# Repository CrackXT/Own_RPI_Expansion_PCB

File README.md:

# Own_RPI_Expansion_PCB

PCB files for RPI Expansion Board

# Description

This is the expansion board for the mainboard.

- Part 2

A small info display is activated via an MCU and the temperature is read from the mainboard. There is also a mic, light sensor and the rotary switch for switching the streamer on and off (and restarting it), as well as status LEDs. 

The RGB is controlled via the MCU. In addition, the MCU can be reset or booted via separate buttons

The board can be produced here (AISLER) with the files (.brd and .sch) or by any other PCB manufacturer. -> https://aisler.net/

# Serie

- .pro

# Layout

Top<br>

Bottom<br>

Routing/Dimensions(mm)<br>

Schematic<br>
Schematic as .pdf at the top of the page.

# License

Open hardware, use it, mod it, whatever you want, feel free...

# Thanks!

Own design and layout.

# Version - Build

v1.0 - 06.11.2023

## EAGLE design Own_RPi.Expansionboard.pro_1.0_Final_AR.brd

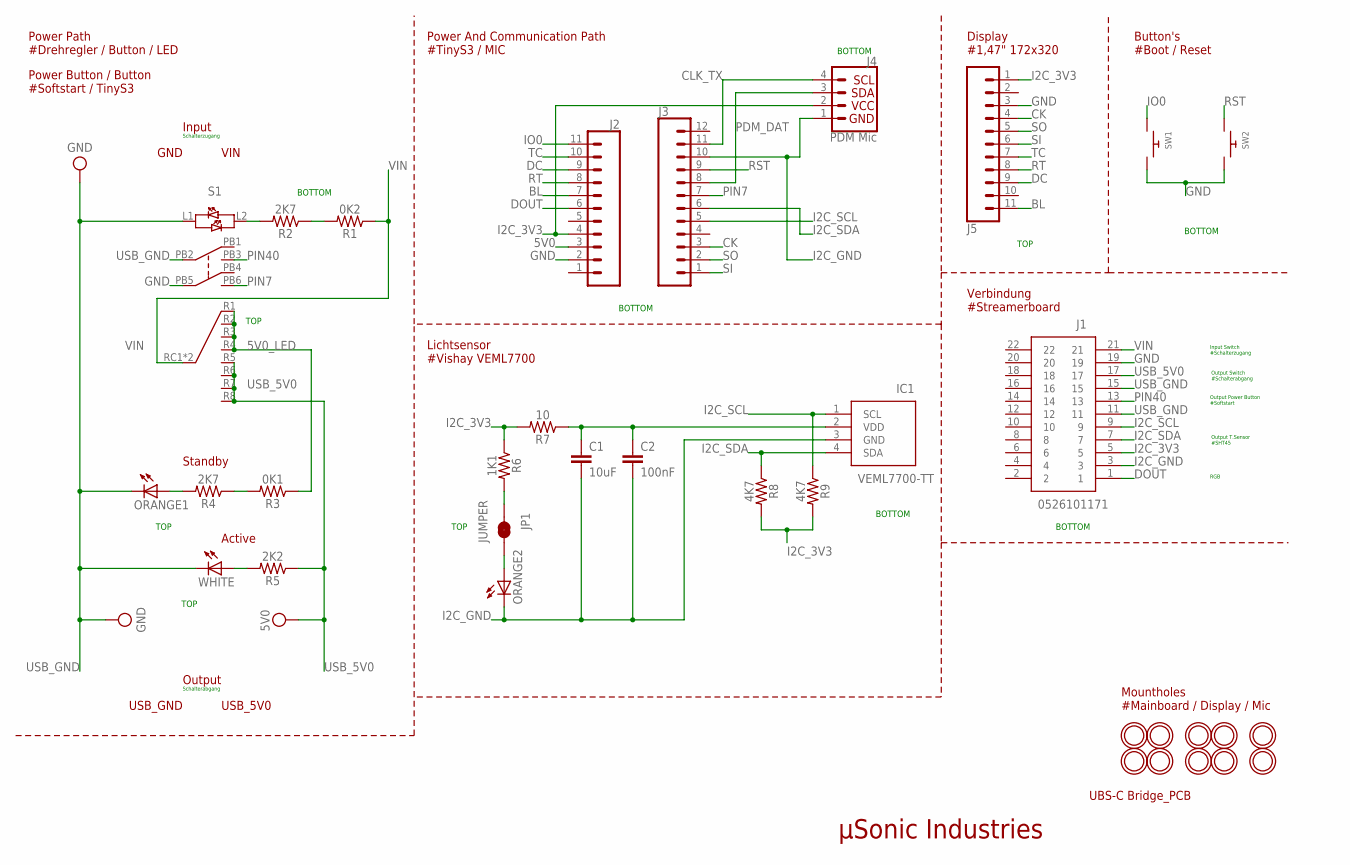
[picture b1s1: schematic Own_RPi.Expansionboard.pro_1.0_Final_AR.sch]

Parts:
C1: 10uF; 0805
C2: 100nF; 0805
IC1: VEML7700-TT; VEML7700
J1: 0526101171
J2, J5: CONN_111X11_NO_SILK; 1X11_NO_SILK
J3: CONN_12NO_SILK; 1X12_NO_SILK
J4: PDM Mic; JST04_1MM_VERT
JP1: JUMPER; SMT-JUMPER_2_NC_TRACE_SILK
ORANGE1, ORANGE2: LEDCHIPLED_0805; CHIPLED_0805
R1: 0K2; 0805
R2, R4: 2K7; 0805
R3: 0K1; 0805
R5: 2K2; 0805
R6: 1K1; 0805
R7: 10; 0805
R8, R9: 4K7; 0805
S1: 481RV12172100
SW1, SW2: SWITCH_PUSHBUTTONSF_OWN; OWN_TACT_PANA-EVQ
U$1, U$2, U$3, U$5, U$8, U$9, U$13, U$14, U$15, U$16: MOUNTINGHOLE2.5; MOUNTINGHOLE_2.5_PLATED
WHITE: LEDCHIPLED_0805; CHIPLED_0805

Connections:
5V0: J2.3
5V0_LED: R3.1, S1.R1, S1.R2, S1.R3, S1.R4
BL: J2.7, J5.11
CK: J3.3, J5.4
CLK_TX: J3.11, J4.4
DC: J2.9, J5.9
DOUT: J1.1, J2.6
GND: J1.19, J2.2, J5.3, S1.PB5, SW1.P$2, SW2.P$2
I2C_3V3: J1.5, J2.4, J4.2, J5.1, R6.1, R7.2, R8.2, R9.2
I2C_GND: C1.2, C2.2, IC1.3 (GND), J1.3, J3.10, J4.1, ORANGE2.C
I2C_SCL: IC1.1 (SCL), J1.9, J3.5, R9.1
I2C_SDA: IC1.4 (SDA), J1.7, J3.6, R8.1
IO0: J2.11, SW1.P$1
unnamed: JP1.2, R6.2
unnamed: R1.2, R2.1
unnamed: R2.2, S1.L2
unnamed: C1.1, C2.1, IC1.2 (VDD), R7.1
unnamed: R3.2, R4.1
unnamed: R5.2, WHITE.A
unnamed: ORANGE1.A, R4.2
unnamed: JP1.1, ORANGE2.A
PDM_DAT: J3.8, J4.3
PIN7: J3.7, S1.PB6
PIN40: J1.13, S1.PB3
RST: J3.9, SW2.P$1
RT: J2.8, J5.8
SI: J3.1, J5.6
SO: J3.2, J5.5
TC: J2.10, J5.7
USB_5V0: J1.17, R5.1, S1.R5, S1.R6, S1.R7, S1.R8
USB_GND: J1.11, J1.15, ORANGE1.C, S1.L1, S1.PB2, WHITE.C
VIN: J1.21, R1.1, S1.RC1 (C1), S1.RC2 (C1)

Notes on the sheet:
µSonic Industries
UBS-C Bridge_PCB
Power Path #Drehregler / Button / LED
Schalterabgang
Mountholes #Mainboard / Display / Mic
Power And Communication Path #TinyS3 / MIC
Power Button / Button #Softstart / TinyS3
Display #1,47" 172x320
Schalterzugang
Input
Output
Standby
Active
USB_GND
VIN
USB_5V0
Button's #Boot / Reset
Input Switch #Schalterzugang
Output Switch #Schalterabgang
Output Power Button #Softstart
RGB
Output T.Sensor #SHT45
GND
Lichtsensor #Vishay VEML7700
BOTTOM
Verbindung #Streamerboard
TOP

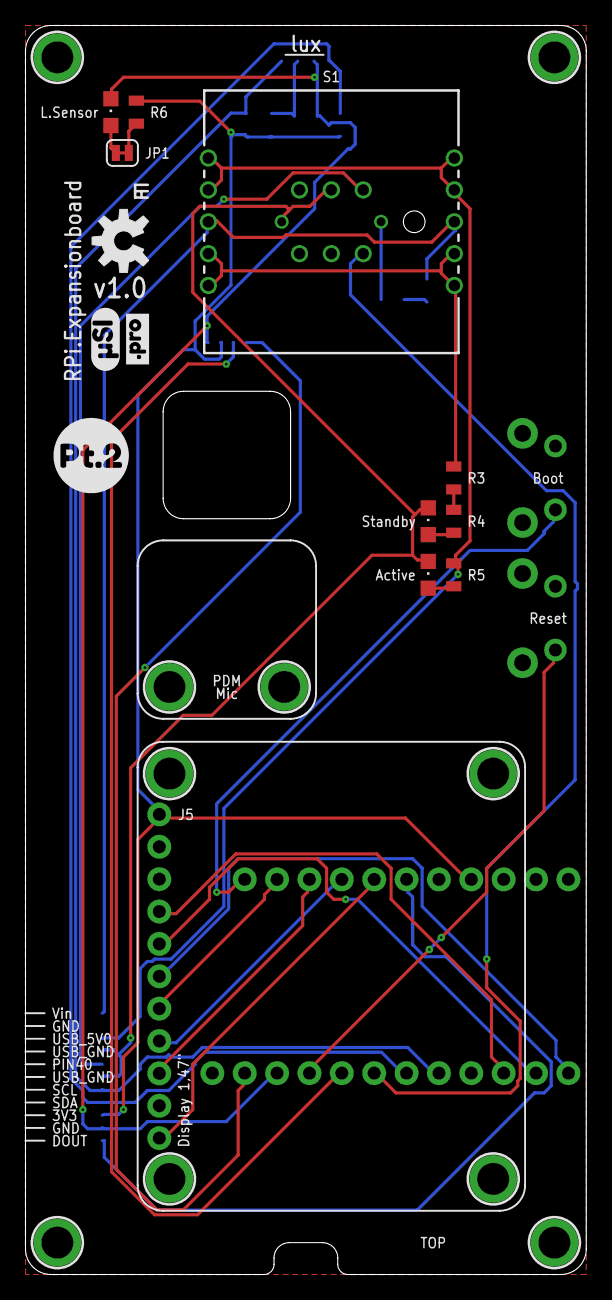
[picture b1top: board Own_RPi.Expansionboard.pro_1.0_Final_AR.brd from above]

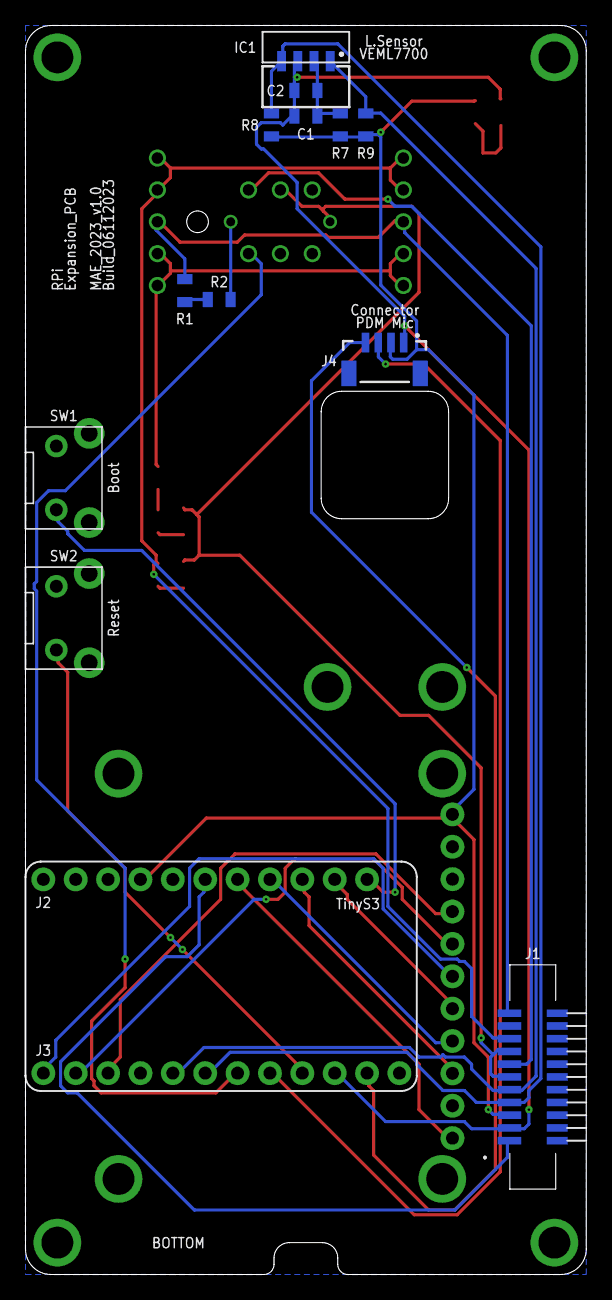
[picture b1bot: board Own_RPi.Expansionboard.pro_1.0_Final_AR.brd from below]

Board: 2 copper layers, 44.0 x 98.0 mm, 38 parts (12 on the bottom side), 31 nets.

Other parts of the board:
U$4: PT.2
U$10: .PRO_LARGE
U$11: µSI_LARGE
U$12: OSHW-LOGO-M

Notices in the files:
parts and their libraries:
microbuilder: This work is placed in the public domain, and may be freely used for commercial and non-commercial work with the following conditions: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
SparkFun-Aesthetics: Licensing: Creative Commons ShareAlike 4.0 International - https://creativecommons.org/licenses/by-sa/4.0
